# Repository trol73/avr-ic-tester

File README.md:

# avr-ic-tester

Тестер цифровых микросхем на atmega32 и дисплее от Nokia 5110

Описание проекта тут: http://trolsoft.ru/sch/ic_tester

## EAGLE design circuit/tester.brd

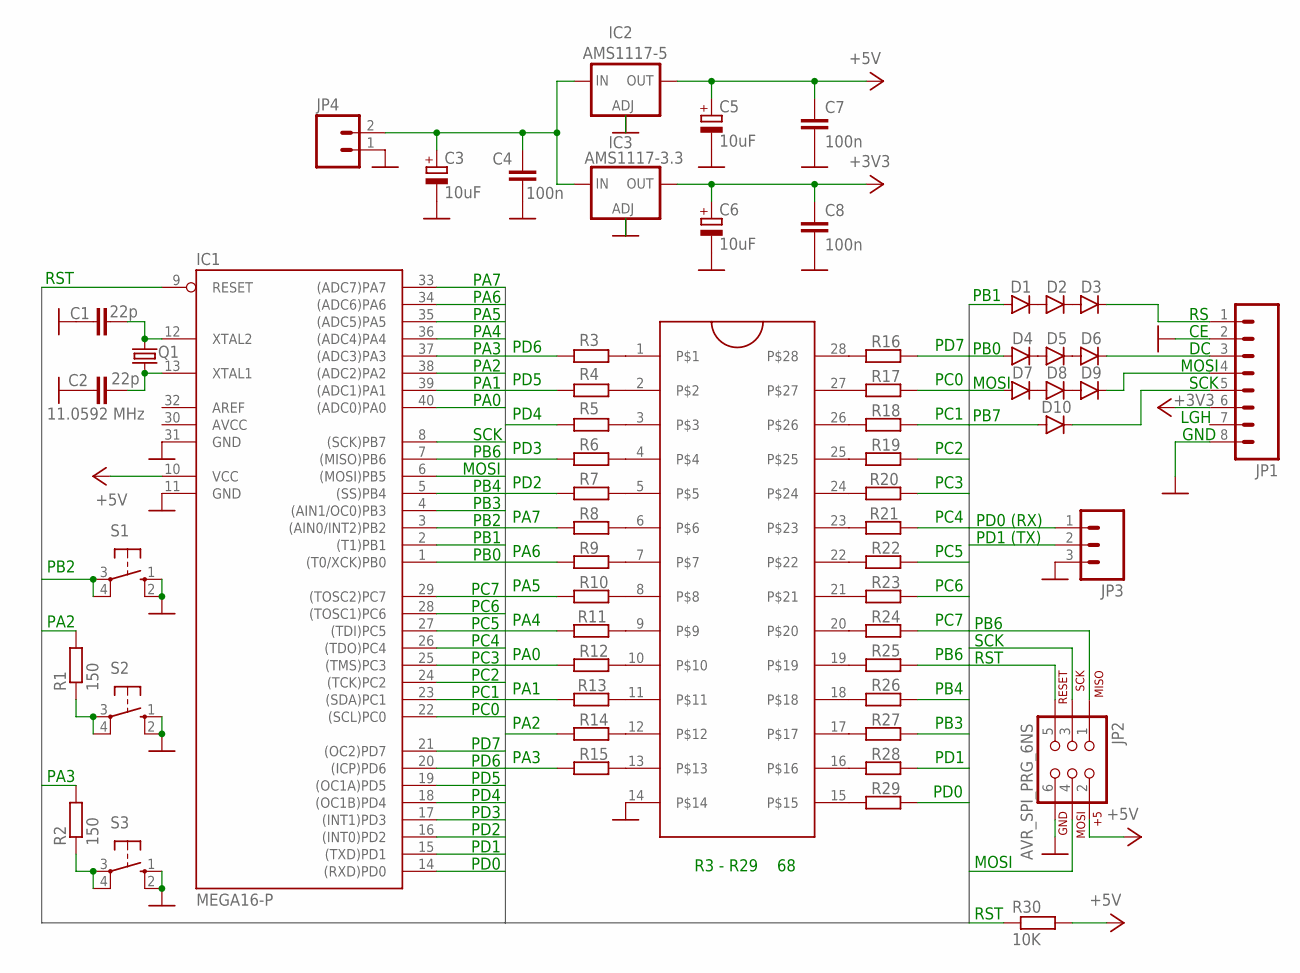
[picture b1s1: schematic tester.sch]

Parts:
C1, C2: 22p; C0805
C3, C5, C6: 10uF; E2,5-5
C4, C7, C8: 100n; C0805
D1, D2, D3, D4, D5, D6, D7, D8, D9, D10: DIODESOD123; SOD-123
IC1: MEGA16-P; DIL40
IC2: AMS1117-5; SOT223
IC3: AMS1117-3.3; SOT223
JP1: M08; 1X08_ROUND
JP2: AVR_SPI_PRG_6NS; 2X3-NS
JP3: M03PTH; 1X03
JP4: M02PTH; 1X02
Q1: 11.0592 MHz; HC49/S
R1, R2: 150; M0805
R3, R4, R5, R6, R7, R8, R9, R10, R11, R12, R13, R14, R15, R16, R17, R18, R19, R20, R21, R22, R23, R24, R25, R26, R27, R28, R29: R-EU_M0805; M0805
R30: 10K; M0805
S1, S2, S3: 10-XX; B3F-10XX
U$1: ZIFSOCKET-28-3ZIFFSOCKET-28-3; DIL28-3-ZIF_SOCKET

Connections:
+3V3: C6.+, C8.1, IC3.4 (OUT), JP1.6
+5V: C5.+, C7.1, IC1.10 (VCC), IC2.4 (OUT), JP2.2, R30.2
AVCC: IC1.30 (AVCC)
GND: C1.1, C2.1, C3.-, C4.1, C5.-, C6.-, C7.2, C8.2, IC1.11 (GND), IC1.31 (GND), IC2.1 (ADJ), IC3.1 (ADJ), JP1.2, JP1.8, JP2.6, JP3.3, JP4.1, S1.1 (S), S1.2 (S1), S2.1 (S), S2.2 (S1), S3.1 (S), S3.2 (S1), U$1.14
unnamed: C2.2, IC1.13 (XTAL1), Q1.1
unnamed: C1.2, IC1.12 (XTAL2), Q1.2
unnamed: R16.2, U$1.28
unnamed: R17.1, U$1.27
unnamed: R18.1, U$1.26
unnamed: R19.1, U$1.25
unnamed: R20.1, U$1.24
unnamed: R21.1, U$1.23
unnamed: R22.1, U$1.22
unnamed: R23.1, U$1.21
unnamed: R24.1, U$1.20
unnamed: R7.1, U$1.5
unnamed: R6.1, U$1.4
unnamed: R5.1, U$1.3
unnamed: R4.1, U$1.2
unnamed: R3.2, U$1.1
unnamed: R8.2, U$1.6
unnamed: R9.2, U$1.7
unnamed: R10.2, U$1.8
unnamed: R11.2, U$1.9
unnamed: R12.2, U$1.10
unnamed: R13.2, U$1.11
unnamed: R14.2, U$1.12
unnamed: R15.2, U$1.13
unnamed: R25.2, U$1.19
unnamed: R26.2, U$1.18
unnamed: R27.1, U$1.17
unnamed: R29.1, U$1.15
unnamed: R28.1, U$1.16
unnamed: C3.+, C4.2, IC2.3 (IN), IC3.3 (IN), JP4.2
unnamed: R2.1, S3.3, S3.4 (P1)
unnamed: R1.1, S2.3, S2.4 (P1)
unnamed: D3.C, JP1.1
unnamed: D1.C, D2.A
unnamed: D2.C, D3.A
unnamed: D6.C, JP1.3
unnamed: D4.C, D5.A
unnamed: D9.C, JP1.4
unnamed: D5.C, D6.A
unnamed: D7.C, D8.A
unnamed: D8.C, D9.A
unnamed: D10.C, JP1.5
PA0: IC1.40 ((ADC0)PA0), R12.1
PA1: IC1.39 ((ADC1)PA1), R13.1
PA2: IC1.38 ((ADC2)PA2), R1.2, R14.1
PA3: IC1.37 ((ADC3)PA3), R2.2, R15.1
PA4: IC1.36 ((ADC4)PA4), R11.1
PA5: IC1.35 ((ADC5)PA5), R10.1
PA6: IC1.34 ((ADC6)PA6), R9.1
PA7: IC1.33 ((ADC7)PA7), R8.1
PB0: D4.A, IC1.1 ((T0/XCK)PB0)
PB1: D1.A, IC1.2 ((T1)PB1)
PB2: IC1.3 ((AIN0/INT2)PB2), S1.3, S1.4 (P1)
PB3: IC1.4 ((AIN1/OC0)PB3), R27.2
PB4: IC1.5 ((SS)PB4), R26.1
PB5: D7.A, IC1.6 ((MOSI)PB5), JP2.4
PB6: IC1.7 ((MISO)PB6), JP2.1, R25.1
PB7: D10.A, IC1.8 ((SCK)PB7), JP2.3
PC0: IC1.22 ((SCL)PC0), R17.2
PC1: IC1.23 ((SDA)PC1), R18.2
PC2: IC1.24 ((TCK)PC2), R19.2
PC3: IC1.25 ((TMS)PC3), R20.2
PC4: IC1.26 ((TDO)PC4), R21.2
PC5: IC1.27 ((TDI)PC5), R22.2
PC6: IC1.28 ((TOSC1)PC6), R23.2
PC7: IC1.29 ((TOSC2)PC7), R24.2
PD0: IC1.14 ((RXD)PD0), JP3.1, R29.2
PD1: IC1.15 ((TXD)PD1), JP3.2, R28.2
PD2: IC1.16 ((INT0)PD2), R7.2
PD3: IC1.17 ((INT1)PD3), R6.2
PD4: IC1.18 ((OC1B)PD4), R5.2
PD5: IC1.19 ((OC1A)PD5), R4.2
PD6: IC1.20 ((ICP)PD6), R3.1
PD7: IC1.21 ((OC2)PD7), R16.1
RESET: IC1.9 (RESET), JP2.5, R30.1

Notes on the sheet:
MOSI
SCK
LGH
GND
PB7
PB6
RST
PB0
PB1
PB2
PA3
PA2
PD6
PD5
PD4
PD3
PD2
PA7
PA6
PA5
PA4
PA0
PA1
PD7
PC0
PC1
PC2
PC3
PC4
PC5
PC6
PC7
PB4
PB3
PD1
PD1 (TX)
PD0
PD0 (RX)
R3 - R29 68

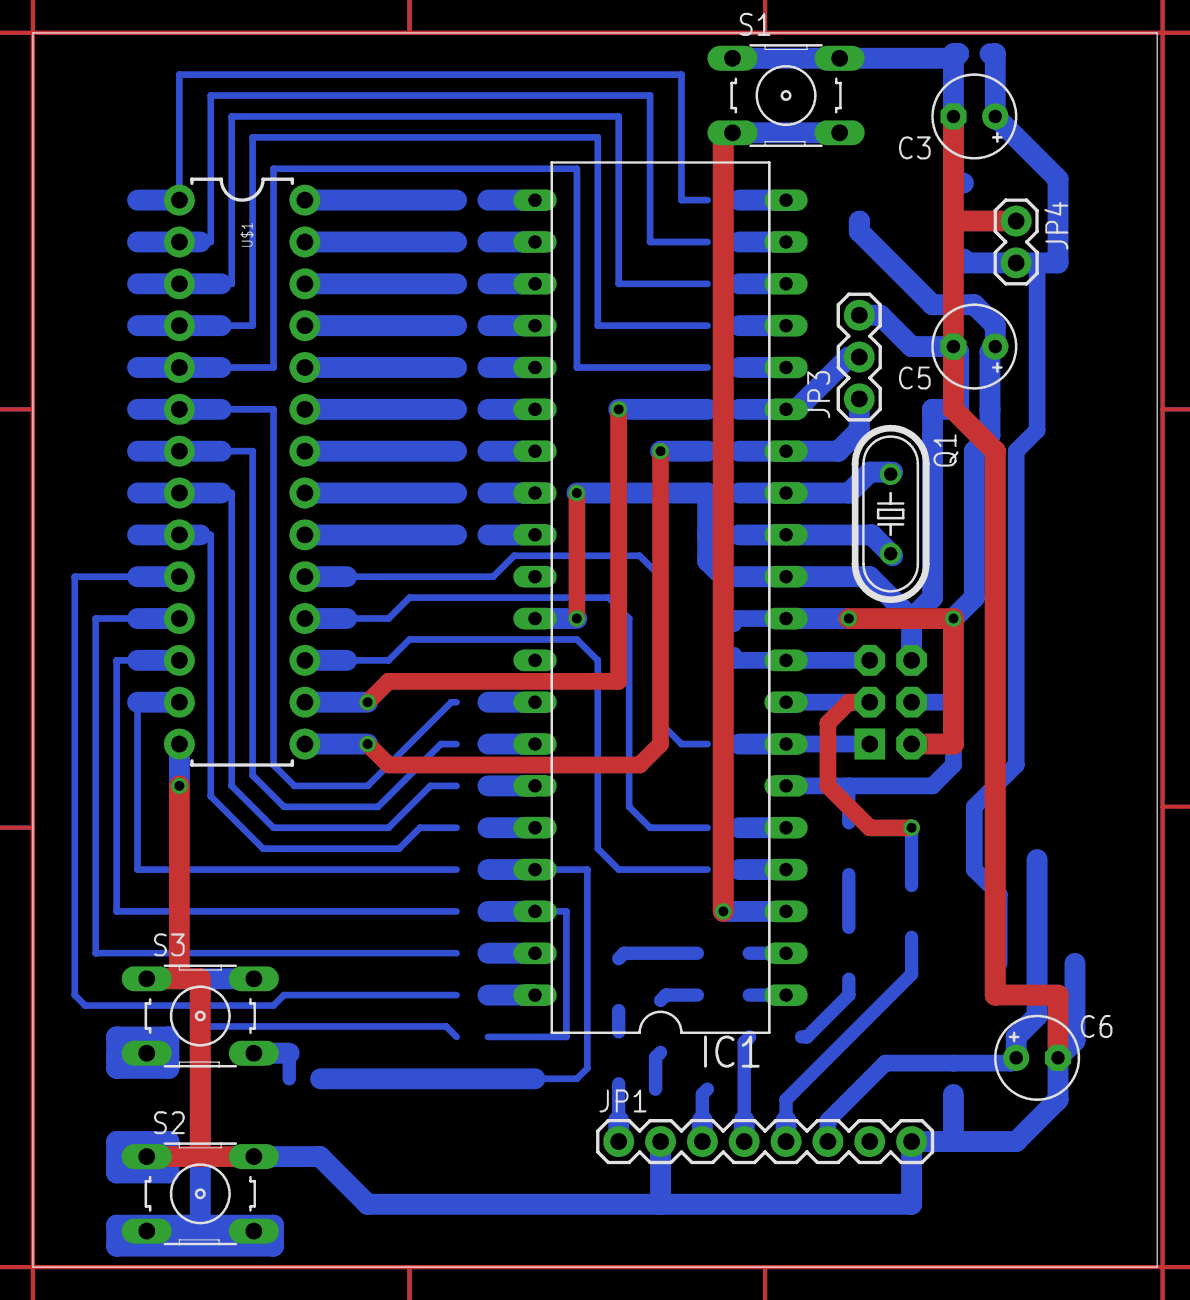
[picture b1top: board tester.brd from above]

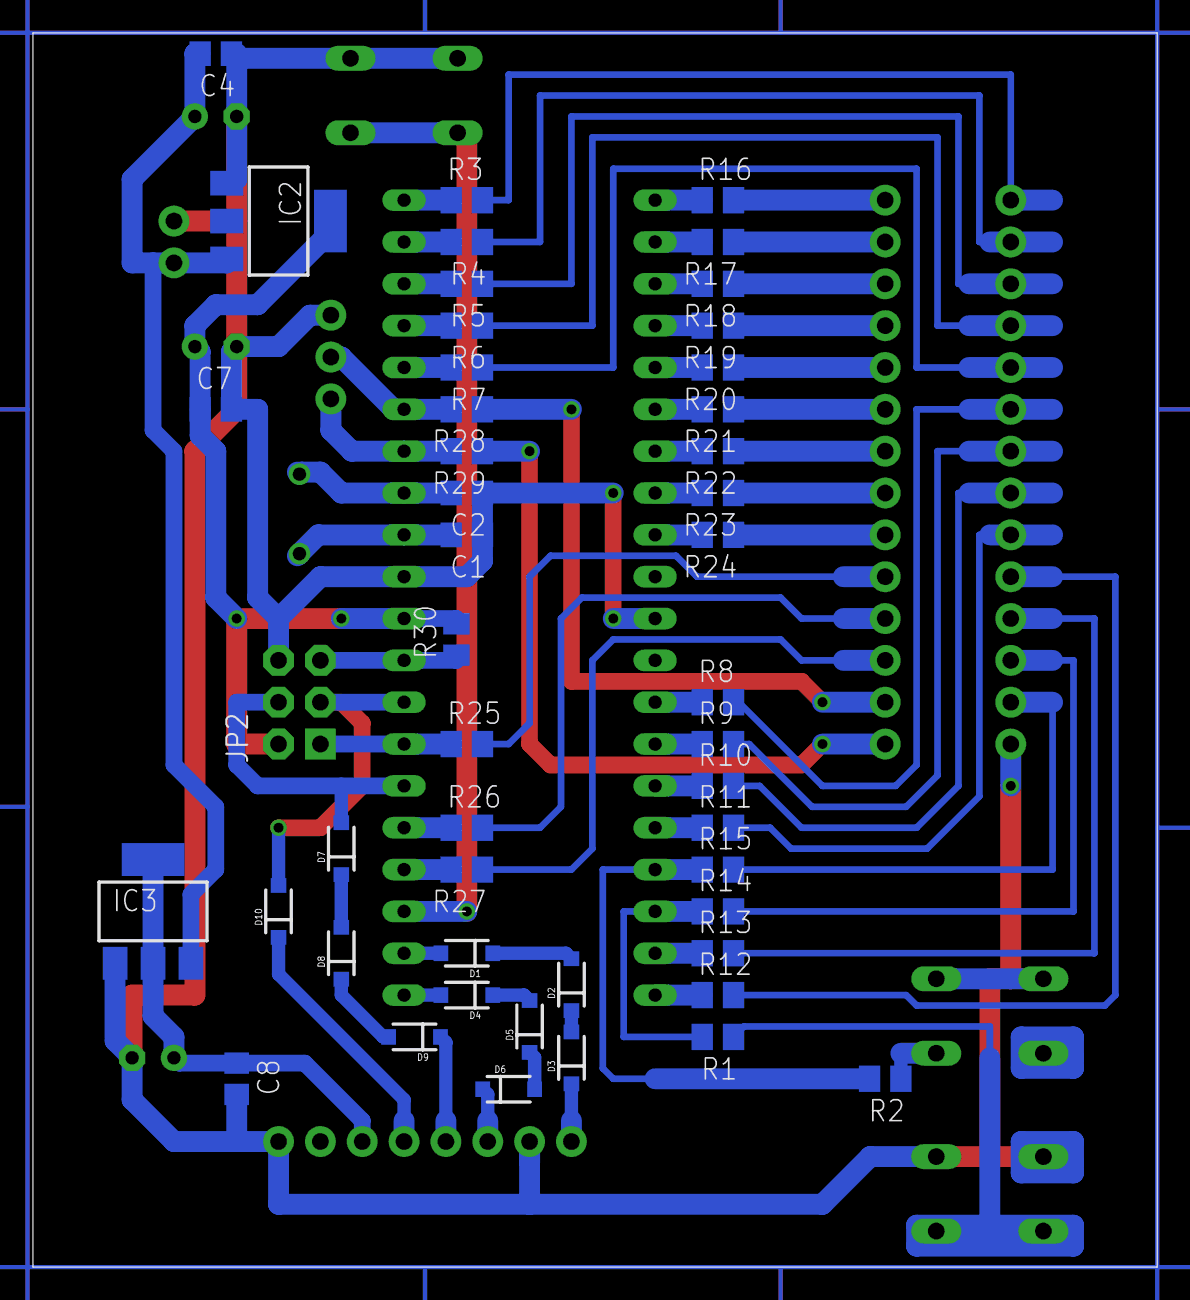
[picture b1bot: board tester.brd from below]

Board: 2 copper layers, 68.2 x 74.9 mm, 60 parts (48 on the bottom side), 78 nets.

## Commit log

2015-07-16 added eagle project
2015-07-18 added script compiler
2015-07-18 used compiled data
2015-07-18 show test results on display updated chips database
2015-07-19 155 ИД 7 команда TEST xxx => yyy
2015-07-19 added 'pulse' command
2015-07-19 частично реализована работа с ИМС с количеством выводов > 16 пока есть ошибки и требуется рефакторинг расширена БД и исправлен компилятор
2015-07-21 оптимизация и приведения кода к единообразию
2015-07-21 рефакторинг завершен, осталось починить работу с DIP-20
2015-07-22 исправлена ошибка проверки DIP-28 проверка ИР23
2015-07-22 добавлен ТВ9
2015-07-23 Добавлены микросхемы
2015-07-24 добавлена заготовка теста РУ-шек
2015-07-24 ИЕ7, ИЕ2
2015-07-26 добавлено несколько микросхем
2015-07-27 заготовка для меню
2015-07-27 добавлены библиотеки
2015-07-27 тест РУ-шек (пока не работает)
2015-07-28 исправлена ошибка подачи питания на РУ-шки
2015-07-28 исправлены методы работы с РУ-шками. написание теста памяти пока в процессе
2015-07-29 работа над тестером РУшек
2015-07-30 тесп памяти готов
2015-07-30 добавлены АП3, АП4, АП5
2015-07-31 добавлены ИР16 и ИР34 тестирование DIP-24 и DIP-28 требует особой работы с клавиатурой, эта логика еще не завершена
2015-08-01 тестирование длинных микросхем завершено
2015-08-01 расширена база тестов
2015-08-03 добавлен КП12
2015-08-04 добавлена схема в pdf
2015-08-07 интерфейс для ручных тестов в процессе
2015-08-08 реализован режим ручного тестирования
2015-08-08 расширена база, исправлен компилятор
2015-08-09 расширена база микросхем компилятор теперь поддерживает микросхемы где входы/выходы могут меняться местами
2015-08-10 HC166
2015-08-10 вывод списка микросхем в базе для компилятора
2015-08-12 рефакторинг компилятора
2015-08-13 оптимизирован компилятор
2015-08-13 добавлены новые команды в прошивку оптимизатор пока не работает
2015-08-14 доделываю компилятор
2015-08-14 исправлен компилятор
2015-08-14 версия 0.5 отключена отладка, исправлены баги
2015-11-02 added gerber files
2015-11-14 added make.builder script
2015-11-17 different build for different display contrast
2015-11-20 added new commands: TEST-Z and TEST-OC
2015-11-20 massive chips base update
2015-11-20 increment version rebuilded chips base
2015-11-22 increased chip name size updated copyright
2015-11-23 Fixed display issues (reproduced with some instances of 5110)
2015-11-23 added TTL & CMOS modes
2015-11-23 added forgotten files
2015-11-23 fixed CMOS test issue
2015-12-02 added 'repeat-pulse' command
2015-12-02 added TTL and CMOS tests
2015-12-03 added new command REPEAT-PULSE
2015-12-05 added delay for REPEAT_PULSE command
2015-12-05 updated gitignore
2015-12-05 fixed compilation of REPEAT_PULSE command
2018-06-29 fixed UI

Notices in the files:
parts and their libraries:
SparkFun-Connectors: Licensing: Creative Commons ShareAlike 4.0 International - https://creativecommons.org/licenses/by-sa/4.0
